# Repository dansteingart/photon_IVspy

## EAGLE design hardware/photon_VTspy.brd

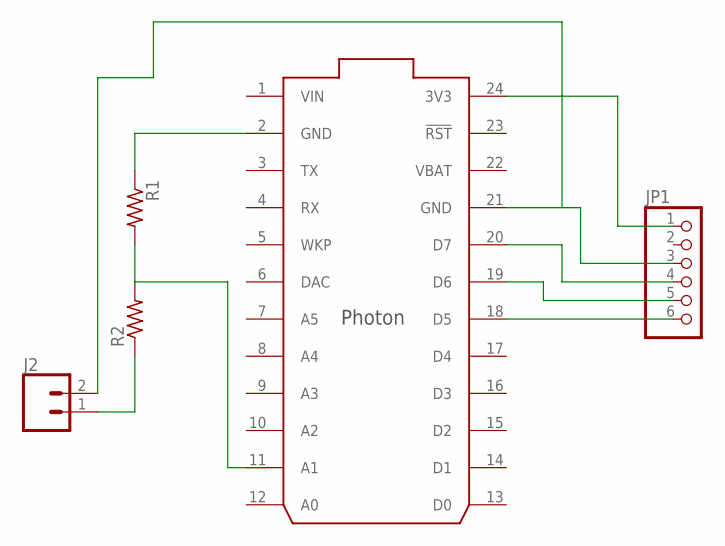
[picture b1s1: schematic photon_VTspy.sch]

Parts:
J2: CONN_023.5MM; SCREWTERMINAL-3.5MM-2
JP1: PINHD-1X6; 1X06
R1, R2: R-US_0207/10; 0207/10
U$1: PHOTON_WITH_HEADERS; PHOTON

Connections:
unnamed: JP1.1, U$1.24 (3V3)
unnamed: JP1.4, U$1.20 (D7)
unnamed: J2.2, JP1.3, U$1.21 (GND)
unnamed: J2.1, R2.1
unnamed: JP1.5, U$1.19 (D6)
unnamed: JP1.6, U$1.18 (D5)
unnamed: R1.1, U$1.2 (GND)
unnamed: R1.2, R2.2, U$1.11 (A1)
VBAT: U$1.22 (VBAT)
VIN: U$1.1 (VIN)

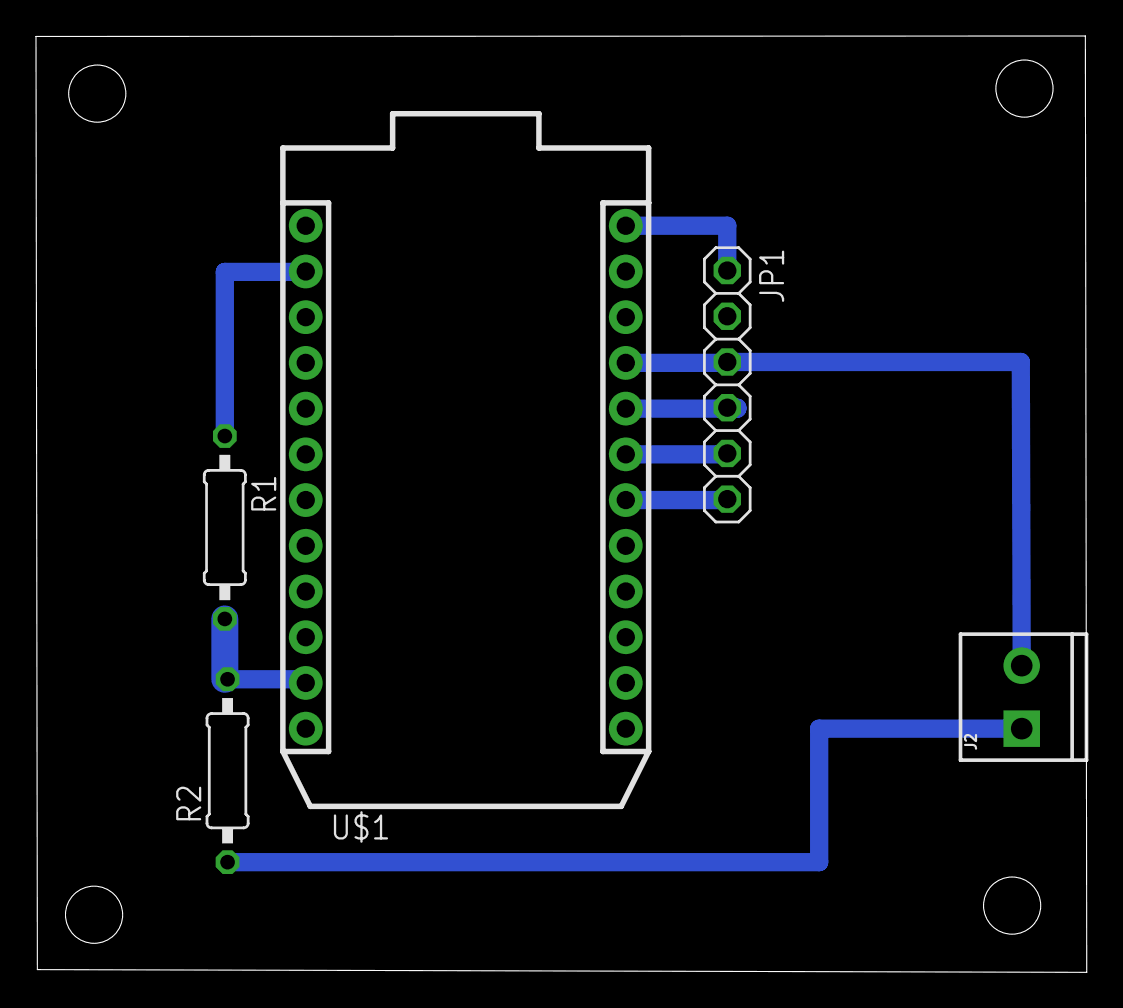
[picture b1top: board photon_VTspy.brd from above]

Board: 2 copper layers, 58.4 x 52.0 mm, 5 parts (0 on the bottom side), 8 nets.

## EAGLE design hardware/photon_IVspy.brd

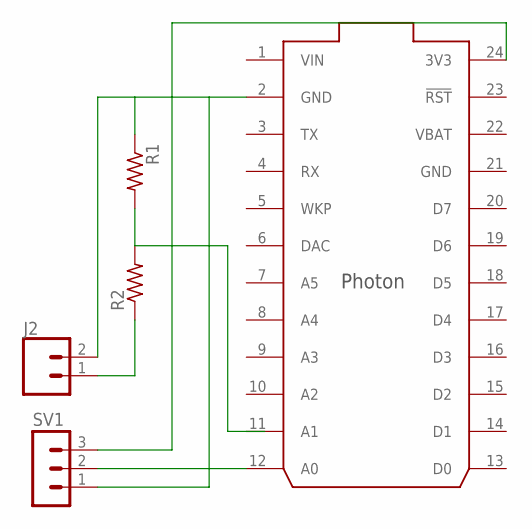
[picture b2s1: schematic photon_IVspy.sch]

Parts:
J2: CONN_023.5MM; SCREWTERMINAL-3.5MM-2
R1, R2: R-US_0207/10; 0207/10
SV1: MA03-1
U$1: PHOTON_WITH_HEADERS; PHOTON

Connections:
GND: U$1.21 (GND)
unnamed: SV1.3, U$1.24 (3V3)
unnamed: SV1.2, U$1.12 (A0)
unnamed: J2.2, R1.1, SV1.1, U$1.2 (GND)
unnamed: J2.1, R2.1
unnamed: R1.2, R2.2, U$1.11 (A1)
VBAT: U$1.22 (VBAT)
VIN: U$1.1 (VIN)

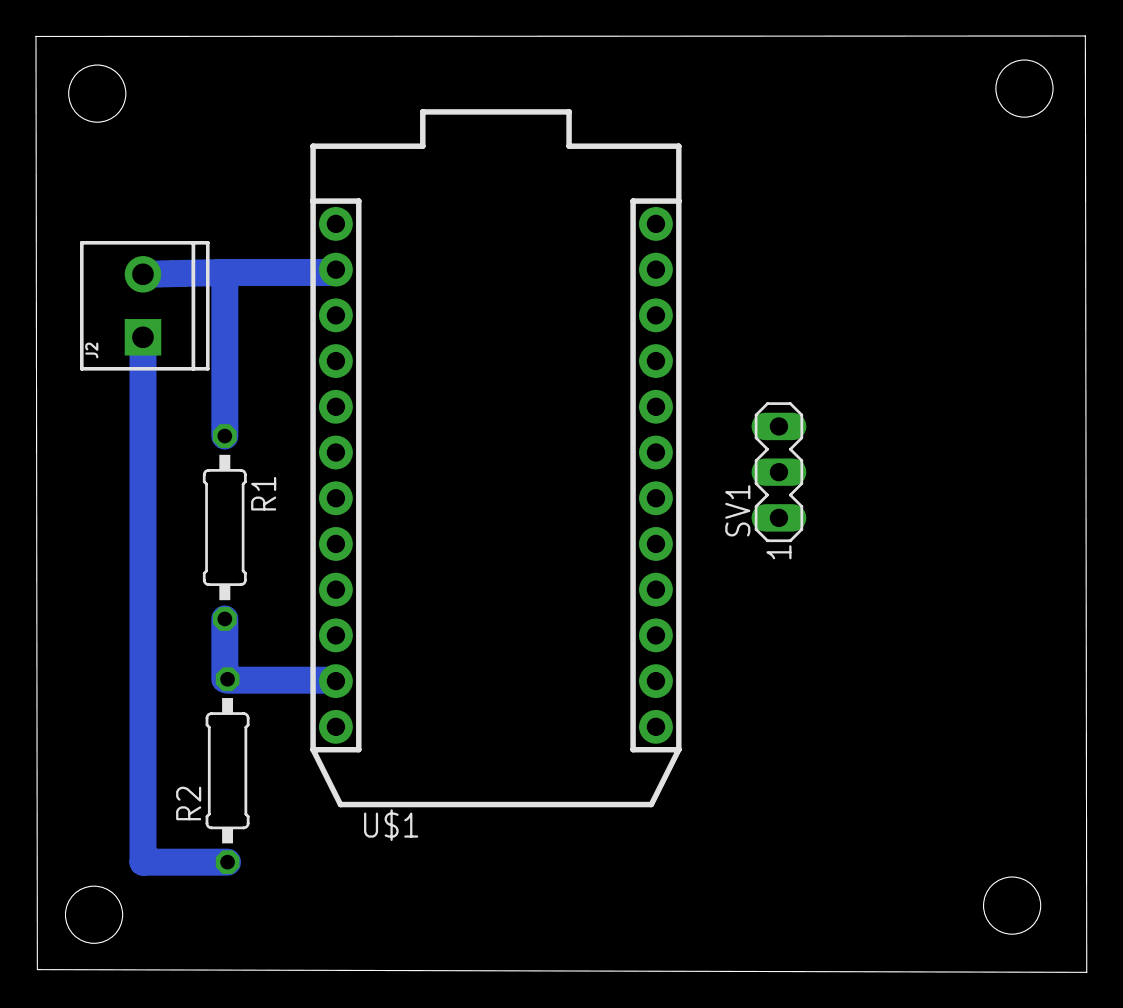
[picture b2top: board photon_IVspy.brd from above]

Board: 2 copper layers, 58.4 x 52.0 mm, 5 parts (0 on the bottom side), 5 nets.

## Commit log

2018-08-24 second push
2018-09-06 board added

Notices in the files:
parts and their libraries:
SparkFun-Connectors: Licensing: Creative Commons ShareAlike 4.0 International - https://creativecommons.org/licenses/by-sa/4.0
